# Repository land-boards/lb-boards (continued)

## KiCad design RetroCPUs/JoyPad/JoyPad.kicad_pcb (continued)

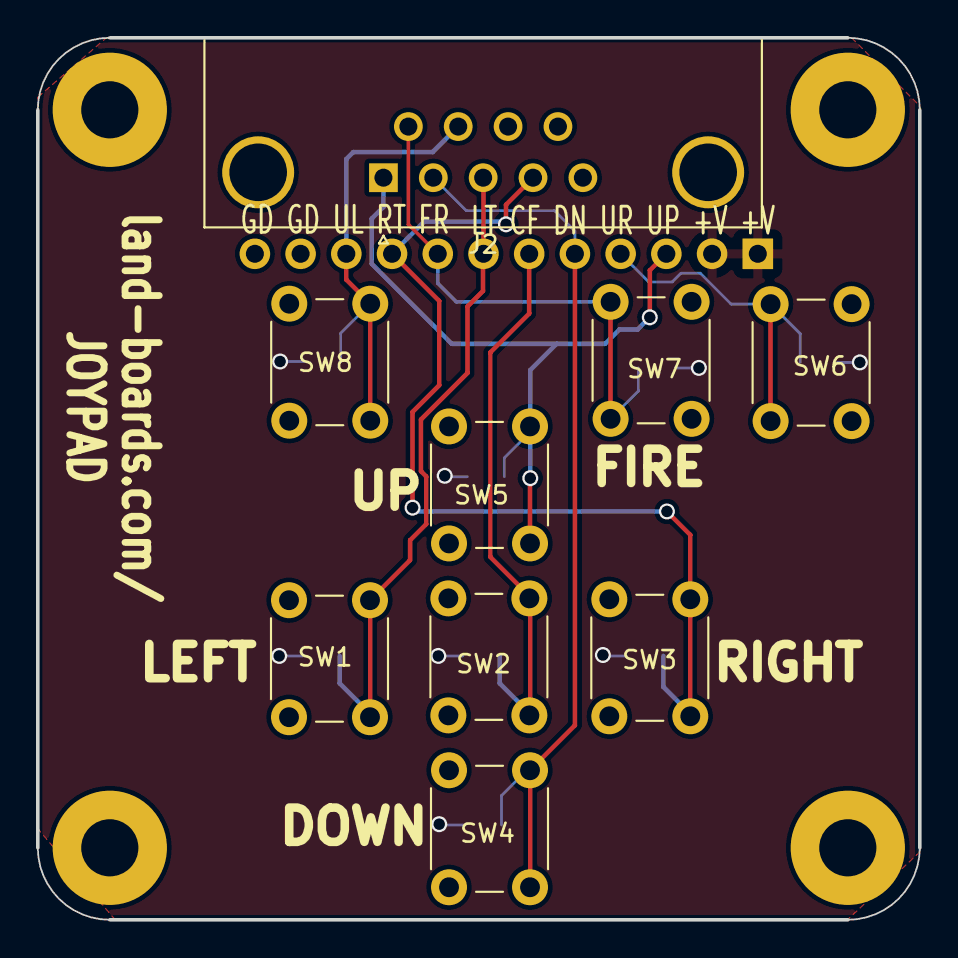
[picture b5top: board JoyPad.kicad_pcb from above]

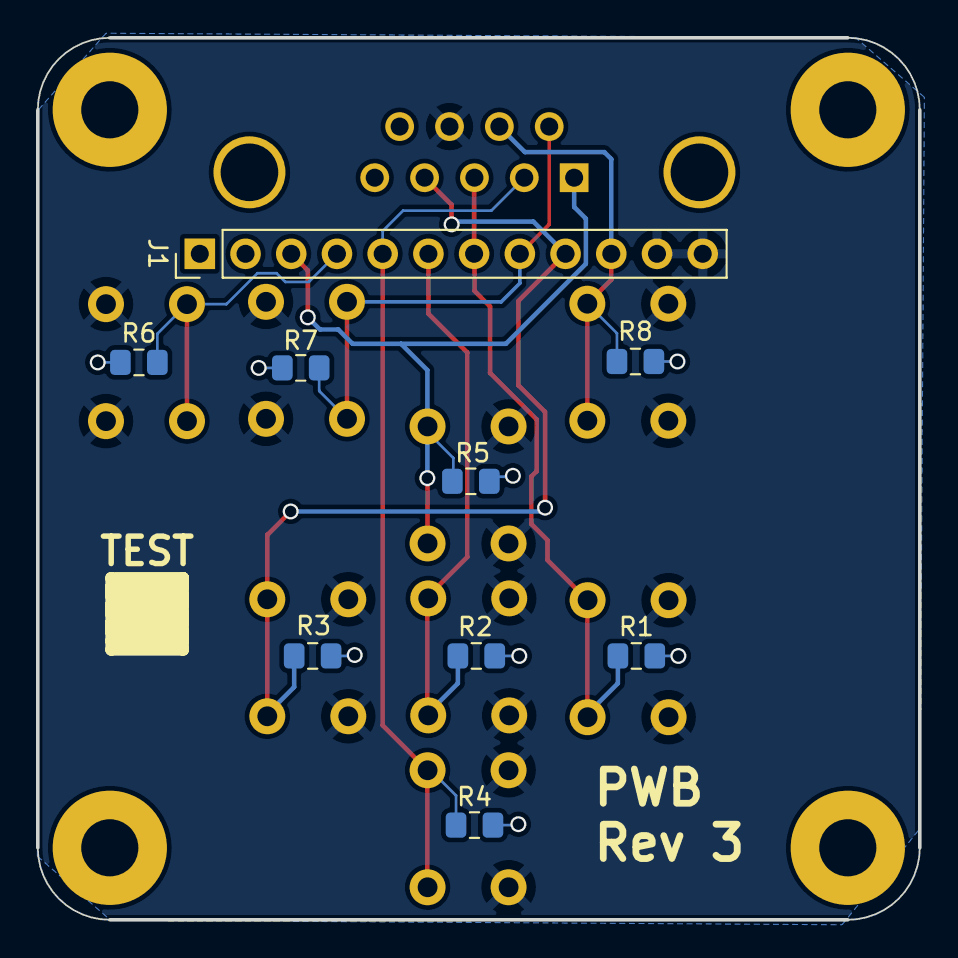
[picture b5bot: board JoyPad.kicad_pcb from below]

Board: 2 copper layers, 49.0 x 49.0 mm, 23 parts (9 on the bottom side), 10 nets.

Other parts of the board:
TEST: CONN_1; TEST_BLK-REAR
